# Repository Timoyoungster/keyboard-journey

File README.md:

# keyboard-journey
*(This repo is for my future self)*
- some crappy plastic full sized keyboard (membrane)
- a sharkoon full sized keyboard (membrane)
- a corsair K70 (mechanical) *not sure about the exact model*
- a razer blackwidow chroma (mechanical; green switches)
- a razer blackwidow chroma (mechanical; orange switches)
- a razer deathstalker pro v2 (mechanical; *i think orange switches*)
- a ferris sweep half-swept (mechanical; Kailh Low Profile Choc Switches Pink (linear / 20gf))

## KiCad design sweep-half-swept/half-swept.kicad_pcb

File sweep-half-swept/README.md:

# Sweep Half Swept

| Front | Back |
| --- | --- |
|  |  |

Half of a Sweep2 with a reversible micro-controller footprint.

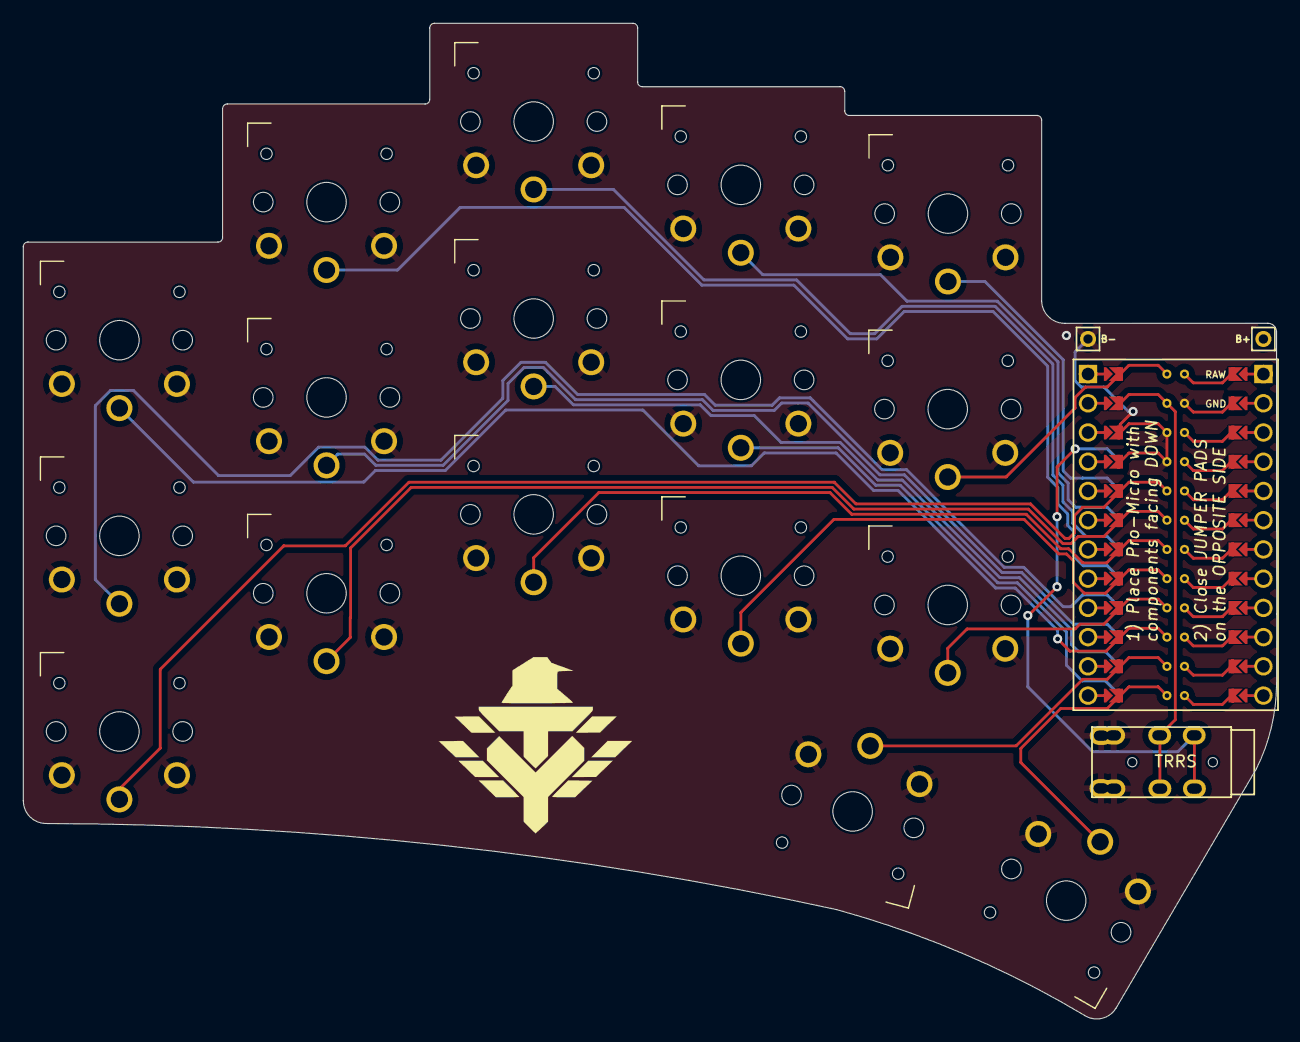
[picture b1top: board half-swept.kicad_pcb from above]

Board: 2 copper layers, 108.9 x 86.5 mm, 21 parts (0 on the bottom side), 20 nets.

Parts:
B+: MountingHole_Pad; 1pin_conn
B-: MountingHole_Pad; 1pin_conn
J2: AudioJack4dpb; TRRS-PJ-DPB2
SW1, SW2, SW3, SW4, SW5, SW6, SW7, SW8, SW9, SW10, SW11, SW12, SW13, SW14, SW15, SW16, SW17: SW_Push; SW_PG1350_rev_DPB
U1: ProMicro-kbd; ProMicro_jumpers_facedown

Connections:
Switch1: SW1.1, U1.10
Switch2: SW2.1, U1.17
Switch3: SW3.1, U1.18
Switch4: SW4.1, U1.19
Switch5: SW5.1, U1.20
Switch6: SW6.1, U1.16
Switch7: SW7.1, U1.15
Switch8: SW8.1, U1.14
Switch9: SW9.1, U1.13
Switch10: SW10.1, U1.1
Switch11: SW11.1, U1.5
Switch12: SW12.1, U1.6
Switch13: SW13.1, U1.7
Switch14: SW14.1, U1.8
Switch15: SW15.1, U1.9
Switch16: SW16.1, U1.11
Switch17: SW17.1, U1.12
Switch18: J2.R1, U1.2
gnd: B-.1, J2.S, J2.T, SW1.2, SW2.2, SW3.2, SW4.2, SW5.2, SW6.2, SW7.2, SW8.2, SW9.2, SW10.2, SW11.2, SW12.2, SW13.2, SW14.2, SW15.2, SW16.2, SW17.2, U1.3, U1.4, U1.23
vcc: J2.R2, U1.21

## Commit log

2023-04-19 adding keyboard history
2023-04-19 adding modified pcb files
2023-04-23 adding keyboard layout ideas
2023-04-26 adding logo to silkscreen
2023-04-26 exported gerber file and sent it to production
2023-04-26 redid the gerber creation with the hole files and resubmitted it to prod
2023-05-23 readme change
2023-05-30 exported stepfile
2023-05-31 adding keymap v1
2023-06-01 removing the not functioning hex file and adding important notes
2023-06-01 keymap changes
2023-06-01 adding escape and hopefulli fixing braces
2023-06-02 adding note regarding the mods
2023-06-02 fixing layout
2023-06-02 usable keymap v1
2023-06-04 README
2023-06-04 gaming mode done
2023-08-05 switching mouse up/down (+wheel) and arrow up/down to match vim bindings, moving mouse 1 to ring finger
2023-10-30 adding case models and notes
2023-10-31 fixing broken quotation marks
2023-11-09 notes
2023-11-09 changing qmk_manual_test to a submodule
2023-11-12 note: noticed bug with arrow mode
